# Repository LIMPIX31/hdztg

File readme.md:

# Hdztg - HD Zero to Tang Mega
Compact adapter for connecting HD Zero compatible cameras to the Sipeed Tang Mega 138K evaluation board for reverse engineering

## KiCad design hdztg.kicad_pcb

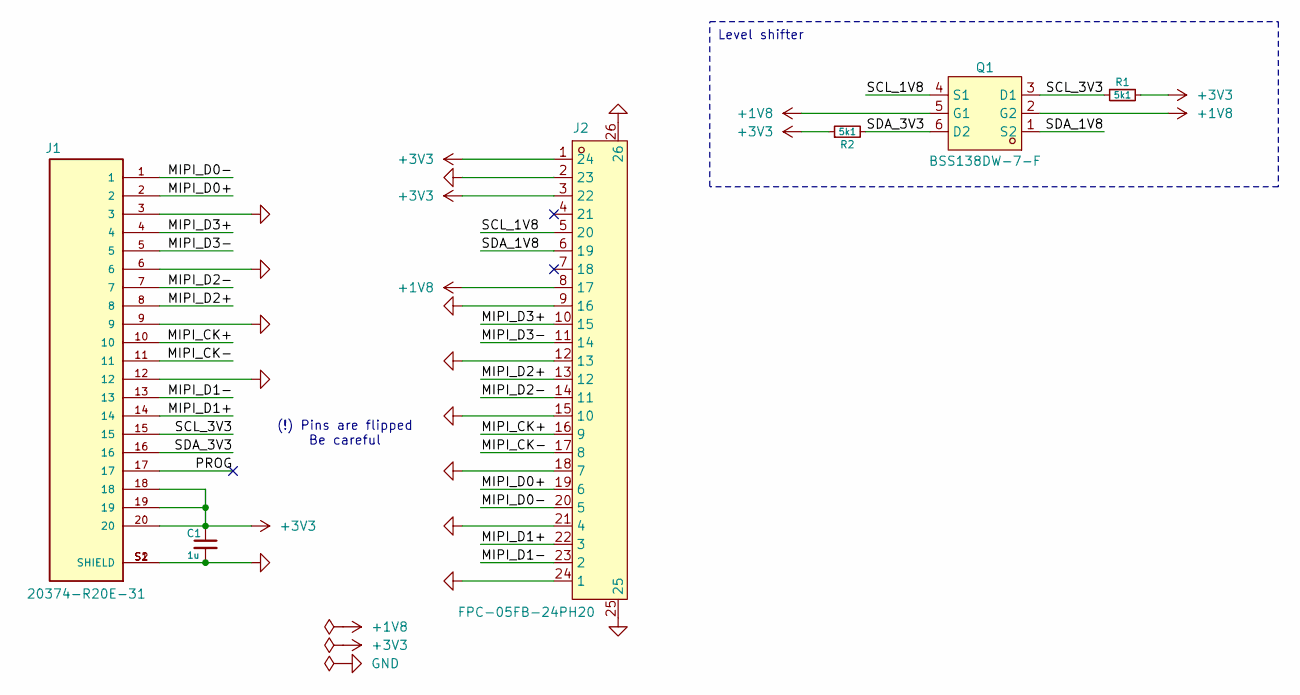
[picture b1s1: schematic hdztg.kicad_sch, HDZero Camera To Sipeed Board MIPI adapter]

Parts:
C1: 1u; C_0402_1005Metric; Manufacturer Part CL05A105KO5NNNC; LCSC C29266
J1: 20374-R20E-31; 20374-R20E-31_I-PEX_20374-R20E-31; Manufacturer Part 20374-R20E-31; DigiKey Part 5378-20374-R20E-31TR-ND
J2: FPC-05FB-24PH20; FPC-SMD_24P-P0.50_FPC-05FB-24PH20; Manufacturer Part FPC-05FB-24PH20; LCSC C2856831
Q1: BSS138DW-7-F; SC-70-6_L2.2-W1.3-P0.65-LS2.1-TL; Manufacturer Part BSS138DW-7-F; LCSC C154900
R1, R2: 5k1; R_0402_1005Metric; Manufacturer Part 0402WGF5101TCE; LCSC C25905

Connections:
+1V8: J2.8 (17), Q1.2 (G2), Q1.5 (G1)
+3V3: C1.1, J1.18, J1.19, J1.20, J2.1 (24), J2.3 (22), R1.2, R2.1
/MIPI_CK+: J1.10, J2.16 (9)
/MIPI_CK-: J1.11, J2.17 (8)
/MIPI_D0+: J1.2, J2.19 (6)
/MIPI_D0-: J1.1, J2.20 (5)
/MIPI_D1+: J1.14, J2.22 (3)
/MIPI_D1-: J1.13, J2.23 (2)
/MIPI_D2+: J1.8, J2.13 (12)
/MIPI_D2-: J1.7, J2.14 (11)
/MIPI_D3+: J1.4, J2.10 (15)
/MIPI_D3-: J1.5, J2.11 (14)
/PROG: J1.17
/SCL_1V8: J2.5 (20), Q1.4 (S1)
/SCL_3V3: J1.15, Q1.3 (D1), R1.1
/SDA_1V8: J2.6 (19), Q1.1 (S2)
/SDA_3V3: J1.16, Q1.6 (D2), R2.2
GND: C1.2, J1.3, J1.6, J1.9, J1.12, J1.S1 (SHIELD), J1.S2 (SHIELD), J2.2 (23), J2.9 (16), J2.12 (13), J2.15 (10), J2.18 (7), J2.21 (4), J2.24 (1), J2.25, J2.26

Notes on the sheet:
Level shifter
(!) Pins are flipped Be careful

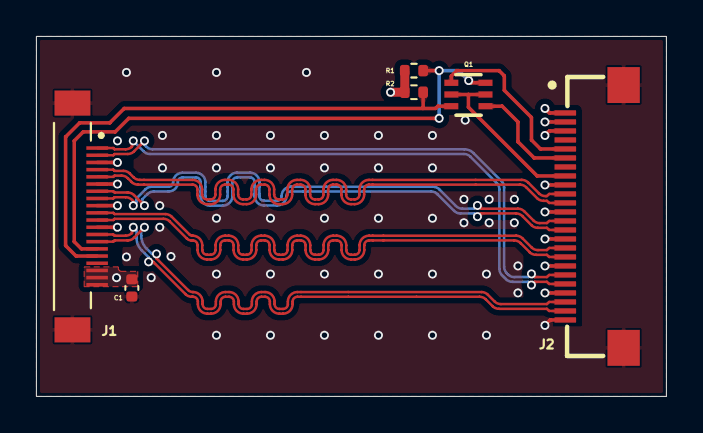
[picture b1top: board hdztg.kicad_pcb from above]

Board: 4 copper layers, 35.0 x 20.0 mm, 6 parts (0 on the bottom side), 17 nets.

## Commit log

2025-07-06 init
2025-07-07 update pcb, fix level shifter
2025-07-09 update pcb
2025-07-12 prod
2025-07-13 fix bottom reference stitching
2025-07-14 manufacturable version (pcb way)
2025-07-21 jlcpcb rev. 1
2025-07-26 jlcpcb production
2025-08-07 readme
